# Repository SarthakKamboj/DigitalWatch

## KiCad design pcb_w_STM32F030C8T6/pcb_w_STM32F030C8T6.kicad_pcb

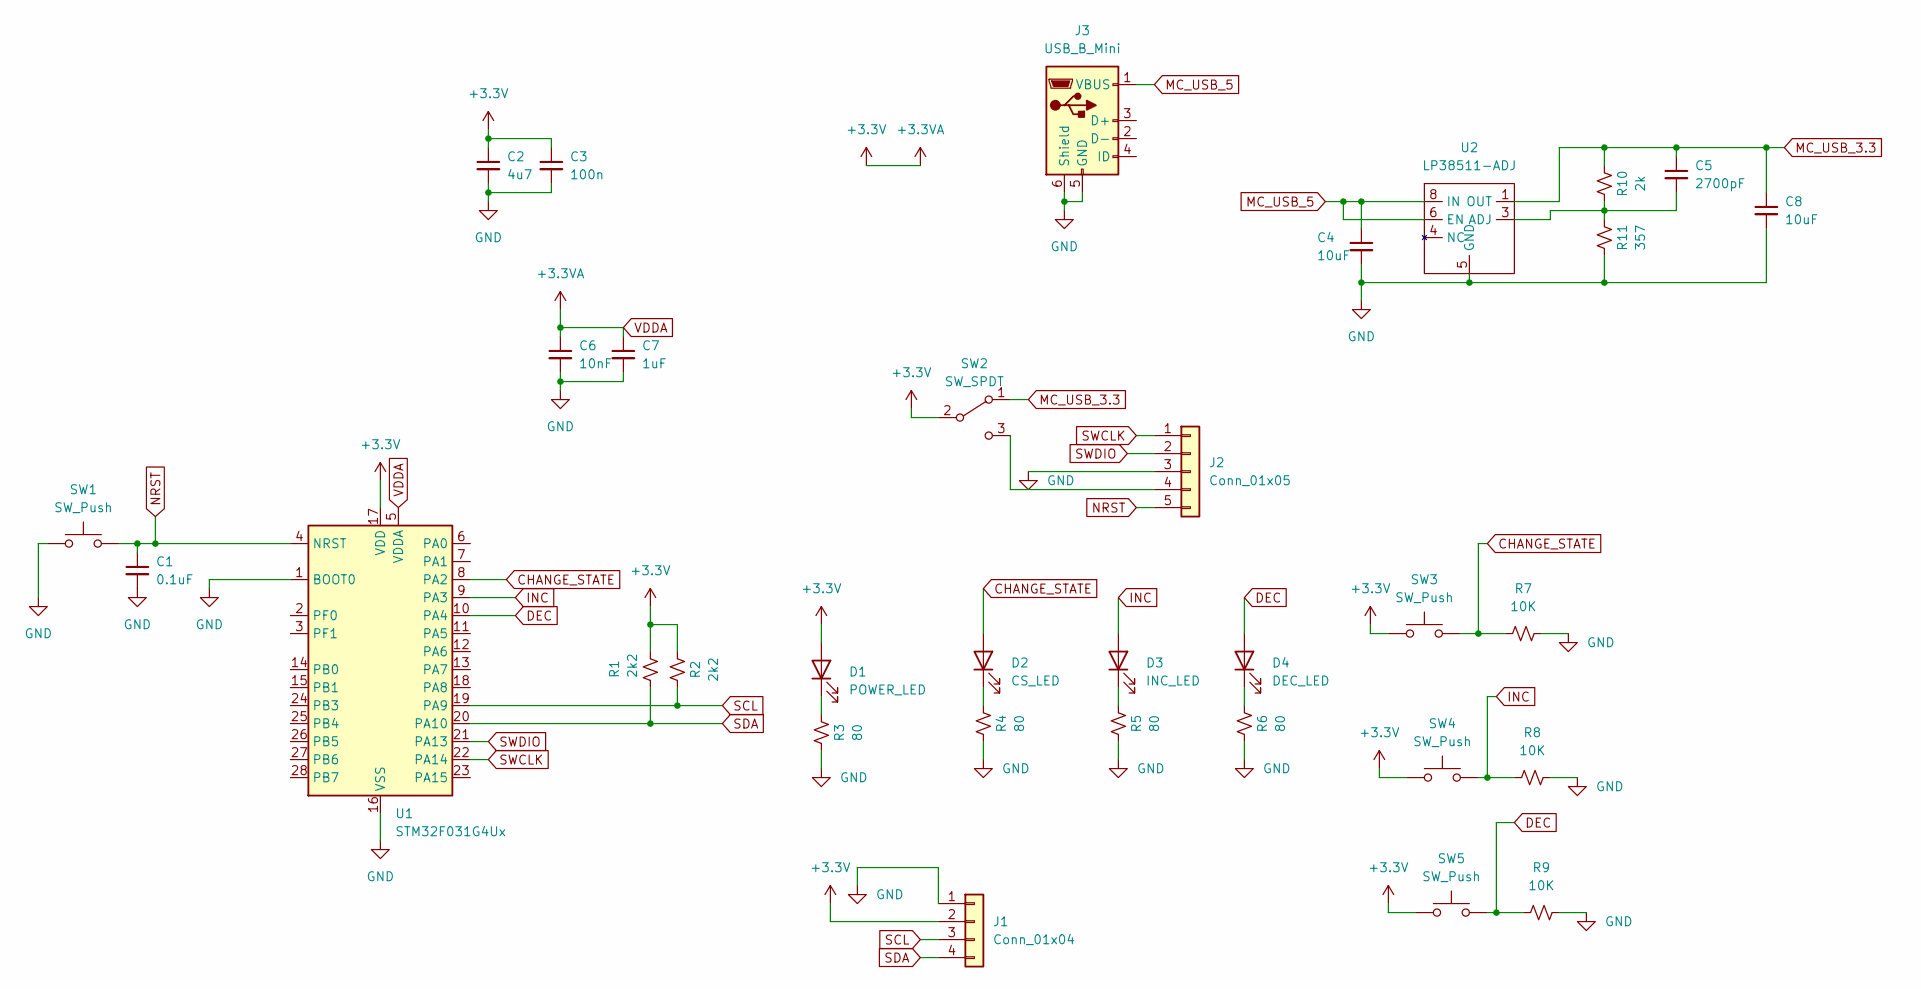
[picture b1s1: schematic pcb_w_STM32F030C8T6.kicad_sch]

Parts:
C1: 0.1uF; C_0805_2012Metric_Pad1.18x1.45mm_HandSolder; DigiKey Part # 0805ZC104KAT2A
C2: 4u7; C_0805_2012Metric_Pad1.18x1.45mm_HandSolder; JLCPCB Part # C1779
C3: 100n; C_0805_2012Metric_Pad1.18x1.45mm_HandSolder; JLCPCB Part # C28233
C4, C8: 10uF; C_0805_2012Metric_Pad1.18x1.45mm_HandSolder; DigiKey Part # CL21A106KPFNNNG
C5: 2700pF; C_0805_2012Metric_Pad1.18x1.45mm_HandSolder; DigiKey Part # C2012C0G2W272J125AA
C6: 10nF; C_0805_2012Metric_Pad1.18x1.45mm_HandSolder; JLCPCB Part # C1710
C7: 1uF; C_0805_2012Metric_Pad1.18x1.45mm_HandSolder; JLCPCB Part # C28323
D1: POWER_LED; D_0805_2012Metric_Pad1.15x1.40mm_HandSolder; JLCPCB Part # C205441
D2: CS_LED; D_0805_2012Metric_Pad1.15x1.40mm_HandSolder; JLCPCB Part # C205441
D3: INC_LED; D_0805_2012Metric_Pad1.15x1.40mm_HandSolder; JLCPCB Part # C205441
D4: DEC_LED; D_0805_2012Metric_Pad1.15x1.40mm_HandSolder; JLCPCB Part # C205441
J1: Conn_01x04; PinSocket_1x04_P2.54mm_Vertical
J2: Conn_01x05; PinHeader_1x05_P2.54mm_Vertical; JLCPCB Part # C124379
J3: USB_B_Mini; USB_Mini-B_Lumberg_2486_01_Horizontal; DigiKey Part # 0548191572
R1, R2: 2k2; R_0805_2012Metric_Pad1.20x1.40mm_HandSolder; JLCPCB Part # C17520
R3, R4, R5, R6: 80; R_0805_2012Metric_Pad1.20x1.40mm_HandSolder; JLCPCB Part # C109433
R7, R8, R9: 10K; R_0805_2012Metric_Pad1.20x1.40mm_HandSolder; JLCPCB Part # C17414
R10: 2k; R_0805_2012Metric_Pad1.20x1.40mm_HandSolder; JLCPCB Part # C17520
R11: 357; R_0805_2012Metric_Pad1.20x1.40mm_HandSolder; JLCPCB Part # C17520
SW1, SW3, SW4, SW5: SW_Push; FSMSMTR-Tactile-Switch-FP; JLCPCB Part # C720477
SW2: SW_SPDT; CL-SB-22A-01T-Slide-Switch-FP; JLCPCB Part # C405952
U1: STM32F031G4Ux; QFN-28_4x4mm_P0.5mm; DigiKey Part # 497-13619-ND
U2: LP38511-ADJ; TI_SO-PowerPAD-8-GND_DAP; DigiKey Part # LP38511MR-ADJ/NOPB

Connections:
CHANGE_STATE: D2.2 (A), R7.1, SW3.2, U1.8 (PA2)
DEC: D4.2 (A), R9.1, SW5.2, U1.10 (PA4)
GND: C1.2, C2.2, C3.2, C4.2, C6.2, C7.2, C8.2, J1.1, J2.3, J3.5 (GND), J3.6 (Shield), R3.1, R4.1, R5.1, R6.1, R7.2, R8.2, R9.2, R11.1, SW1.1, U1.1 (BOOT0), U1.16 (VSS), U2.5 (GND)
INC: D3.2 (A), R8.1, SW4.2, U1.9 (PA3)
MC_USB_3.3: C5.1, C8.1, R10.2, SW2.1 (A), U2.1 (OUT)
MC_USB_5: C4.1, J3.1 (VBUS), U2.6 (EN), U2.8 (IN)
NRST: C1.1, J2.5, SW1.2, U1.4 (NRST)
unnamed: C5.2, R10.1, R11.2, U2.3 (ADJ)
unnamed: D1.1 (K), R3.2
unnamed: D2.1 (K), R4.2
unnamed: D3.1 (K), R5.2
unnamed: D4.1 (K), R6.2
unnamed: J2.4, SW2.3 (C)
SCL: J1.3, R2.1, U1.19 (PA9)
SDA: J1.4, R1.1, U1.20 (PA10)
SWCLK: J2.1, U1.22 (PA14)
SWDIO: J2.2, U1.21 (PA13)
VDDA: C2.1, C3.1, C6.1, C7.1, D1.2 (A), J1.2, R1.2, R2.2, SW2.2 (B), SW3.1, SW4.1, SW5.1, U1.5 (VDDA), U1.17 (VDD)

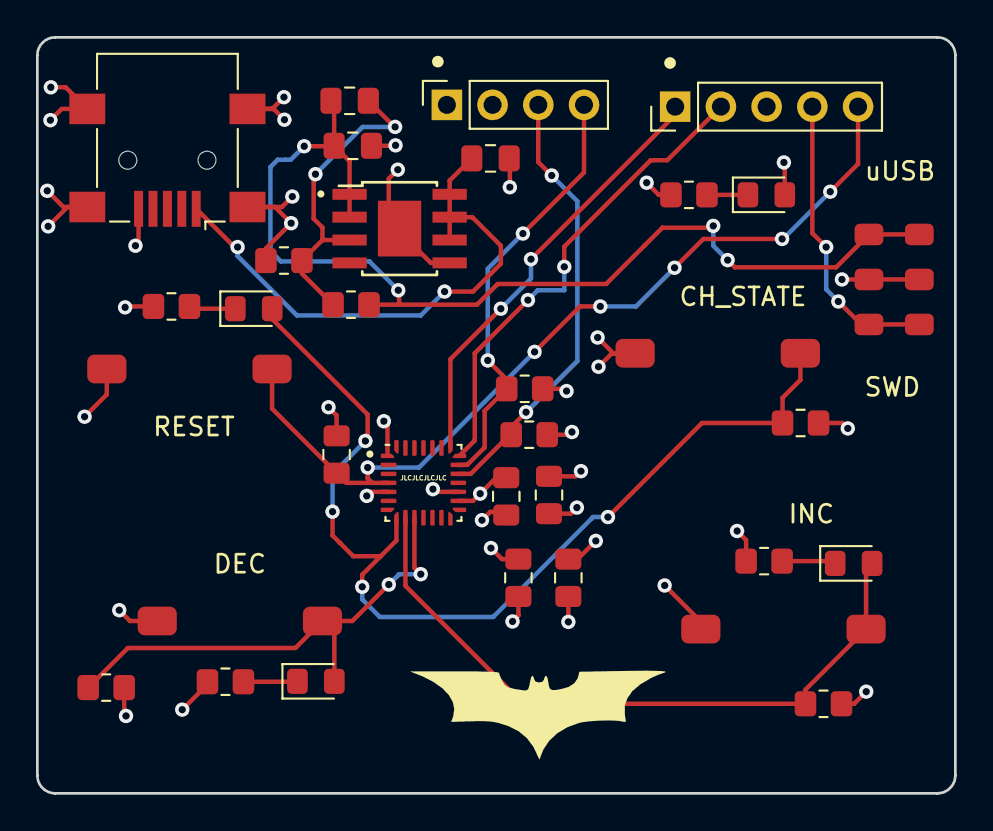
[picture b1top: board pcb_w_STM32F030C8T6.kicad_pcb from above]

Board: 4 copper layers, 51.0 x 42.0 mm, 33 parts (0 on the bottom side), 18 nets.

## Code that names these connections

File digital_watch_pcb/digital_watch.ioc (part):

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Mcu.Name=STM32F031G(4-6)Ux
Mcu.Package=UFQFPN28
Mcu.UserName=STM32F031G4Ux
PA10.Mode=I2C
PA10.Signal=I2C1_SDA
PA13.Mode=Serial_Wire
PA13.Signal=SYS_SWDIO
PA14.Mode=Serial_Wire
PA14.Signal=SYS_SWCLK
PA2.GPIOParameters=GPIO_Label
PA2.GPIO_Label=CHG_STATE
PA2.Signal=GPXTI2
PA3.GPIOParameters=GPIO_Label
PA3.GPIO_Label=INC
PA3.Signal=GPXTI3
PA4.GPIOParameters=GPIO_Label
PA4.GPIO_Label=DEC
PA4.Signal=GPXTI4
PA9.Mode=I2C
PA9.Signal=I2C1_SCL
board=custom

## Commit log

2022-03-27 numbers displaying on oled
2022-03-29 made horizontal offsets more flexible
2022-03-29 added text size
2022-03-29 removed comments
2022-03-29 added Debug to .gitignore
2022-03-29 removed build stuff
2022-03-29 made slash look better
2022-03-31 centered text and timer replaying
2022-04-14 refactored code and made stopwatch
2022-04-14 removed more comments
2022-04-14 made changing value blink and added time changing interrupt
2022-04-15 moved stuff around and added folder for pcb
2022-04-16 did basic setup on stm and added scl and sda lines
2022-04-16 moved time change interrupt code to time.c
2022-04-17 finished everything but usb power up
2022-04-17 can decrements numbers now
2022-04-17 added buttons
2022-04-18 added to circuit, added pcb and code folders for STM32F030C8T6
2022-04-18 added ldo...created some footprints...and currently doing routing
2022-04-18 made board 4 layers
2022-04-18 saved
2022-04-18 finished routing...need to fix margins errors
2022-04-18 finished routing and add silkscreen
2022-04-18 added batman logo
2022-04-19 changing components and mc to ones in stock at digikey
2022-04-20 changing linear regulator
2022-04-20 finished schematic fixes and finished pcb
2022-04-20 misc
2022-04-20 renamed stuff
